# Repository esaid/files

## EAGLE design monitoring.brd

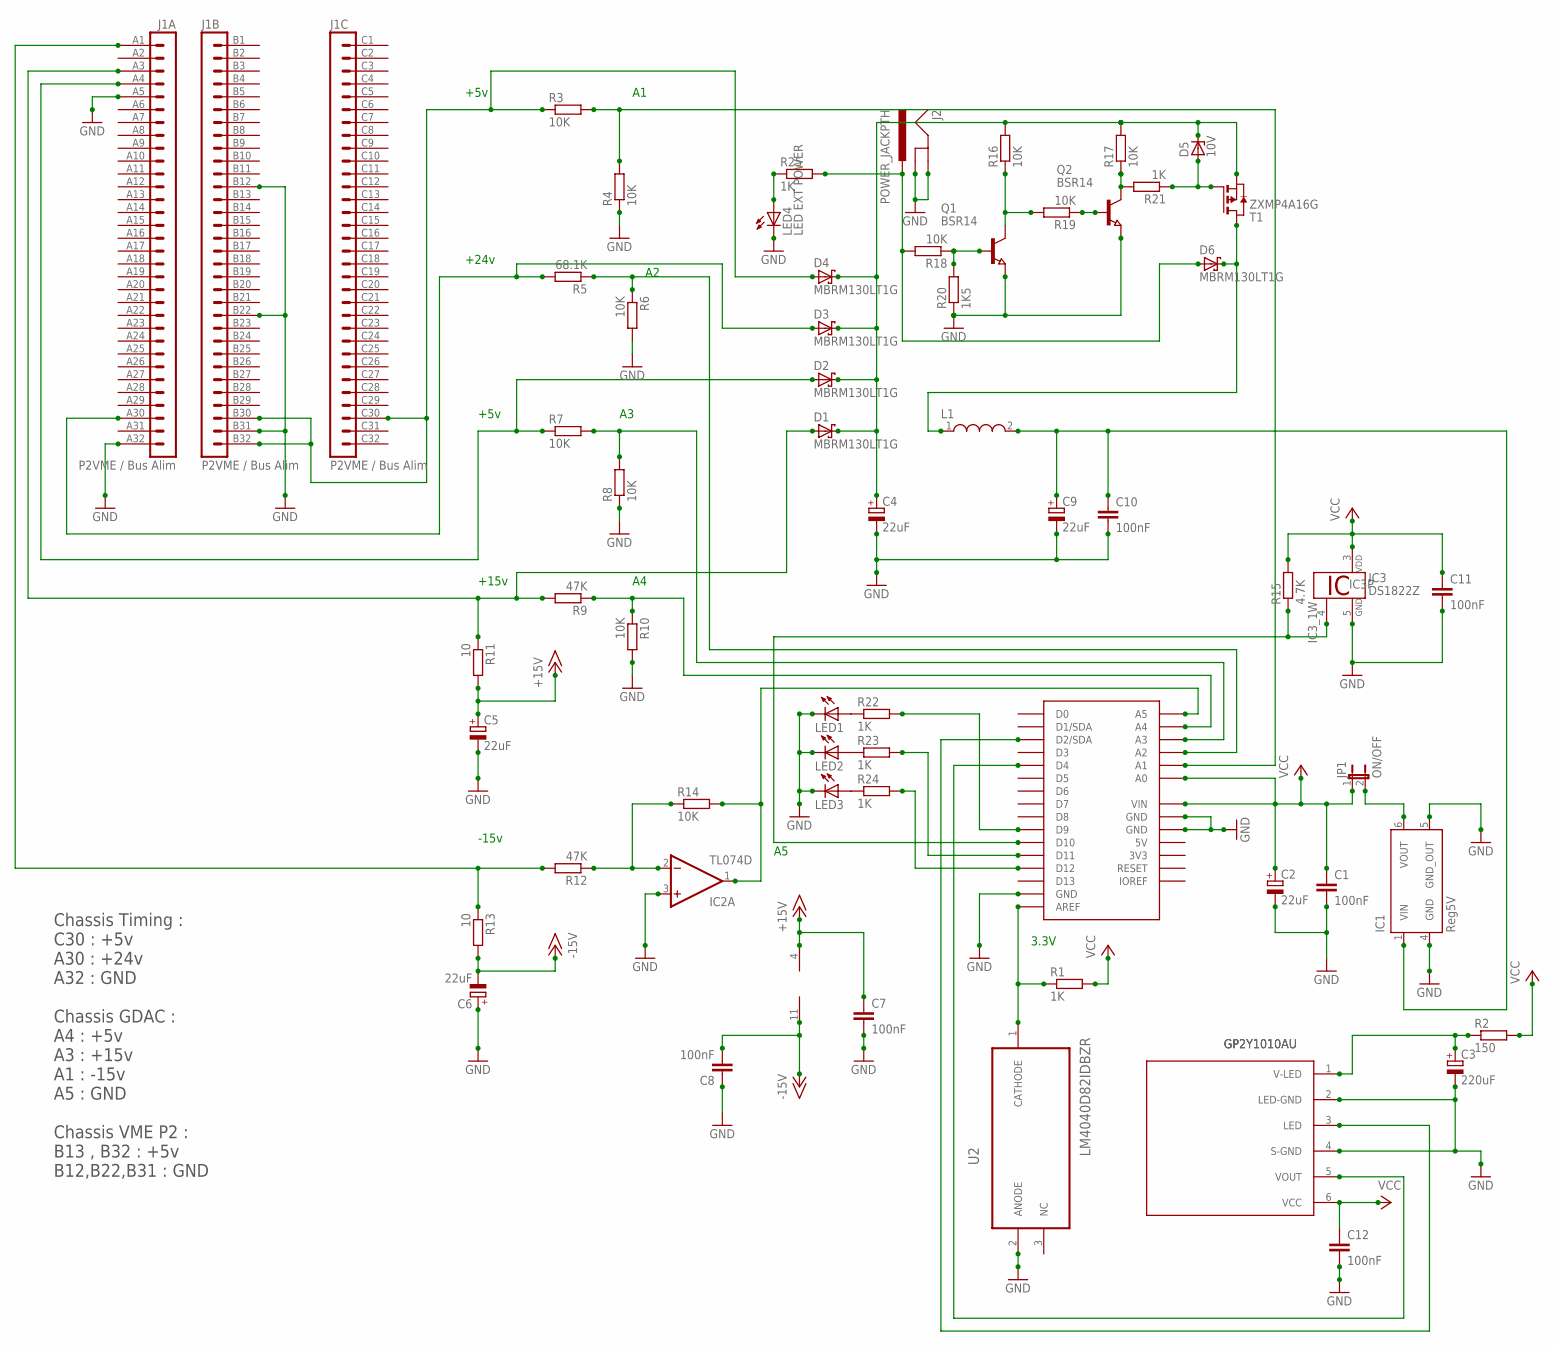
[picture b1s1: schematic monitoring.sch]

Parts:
C1, C7, C8, C10, C11, C12: 100nF; C1206K
C2, C4, C5, C6, C9: 22uF; CT7343
C3: 220uF; 150CLZ-0810
D1, D2, D3, D4, D6: MBRM130LT1G; DIODE_SMB
D5: 10V; SMB
IC1: Reg5V; REG5V
IC2: TL074D; SO14
IC3: DS1822Z; SO08
J1: P2VME / Bus Alim; VG96
J2: POWER_JACKPTH; POWER_JACK_PTH
JP1: ON/OFF; JP1
L1: WE-UKW_1SW_7427501; WE-UKW_7427501
LED1, LED2, LED3: LED_ELD260; LED_LD260
LED4: LED EXT POWER; LED_LD260
Q1, Q2: BSR14; SOT23
R1, R21, R22, R23, R24, R25: 1K; R1206
R2: 150; R1206
R3, R4, R6, R7, R8, R10, R14, R16, R17, R18, R19: 10K; R1206
R5: 68.1K; R1206
R9, R12: 47K; R1206
R11, R13: 10; R1206
R15: 4.7K; R1206
R20: 1K5; R1206
T1: ZXMP4A16G; SOT223
U1: YUN_SHIELD-BPLACE; YUN_SHIELD
U2: LM4040D82IDBZR; SOT95P237X112-3N
U$1: GP2Y1010AU0F; GP2Y1010AU

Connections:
3V3: U1.3V3
5V: U1.5V
+15V: C5.+, C7.1, IC2.4 (V+), R11.2
-15V: C6.-, C8.2, IC2.11 (V-), R13.2
GND: C1.2, C2.-, C3.-, C4.-, C5.-, C6.+, C7.2, C8.1, C9.-, C10.2, C11.2, C12.2, IC1.4 (GND), IC1.5 (GND_OUT), IC2.3 (+IN), IC3.5 (GND), J1.A5 (5), J1.A32 (32), J1.B12 (12), J1.B22 (22), J1.B31 (31), J2.GND, J2.GNDBREAK, LED1.K (C), LED2.K (C), LED3.K (C), LED4.K (C), Q1.2 (E), Q2.2 (E), R4.1, R6.2, R8.1, R10.2, R20.1, U1.GND@1 (GND), U1.GND@2 (GND), U1.GND@3 (GND), U2.2 (ANODE), U$1.2 (LED-GND), U$1.4 (S-GND)
IOREF: U1.IOREF
unnamed: C3.+, R2.1, U$1.1 (V-LED)
unnamed: IC1.6 (VOUT), JP1.2
unnamed: R1.1, U1.AREF, U2.1 (CATHODE)
unnamed: R3.2, R4.2, U1.A1
unnamed: R5.1, R6.1, U1.A2
unnamed: R7.2, R8.2, U1.A3
unnamed: R9.1, R10.1, U1.A4
unnamed: Q1.1 (B), R18.1, R20.2
unnamed: D3.A (C), J1.A30 (30), R5.2
unnamed: D2.A (C), J1.A4 (4), R7.1
unnamed: D1.A (C), J1.A3 (3), R9.2, R11.1
unnamed: C4.+, D1.C (A), D2.C (A), D3.C (A), D4.C (A), D5.C, R16.2, R17.2, T1.3 (S)
unnamed: D4.A (C), J1.B30 (30), J1.B32 (32), J1.C30 (30), R3.1
unnamed: IC2.2 (-IN), R12.1, R14.1
unnamed: J1.A1 (1), R12.2, R13.1
unnamed: IC2.1 (OUT), R14.2, U1.A5
unnamed: D6.C (A), L1.1, T1.2 (D), T1.4 (D)
unnamed: LED1.A, R22.1
unnamed: C9.+, C10.1, IC1.1 (VIN), L1.2
unnamed: Q2.3 (C), R17.1, R21.2
unnamed: Q2.1 (B), R19.1
unnamed: Q1.3 (C), R16.1, R19.2
unnamed: D5.A, R21.1, T1.1 (G)
unnamed: IC3.4 (1W), R15.1, U1.D10
unnamed: U1.D2 (D2/SDA), U$1.3 (LED)
unnamed: U1.D4, U$1.5 (VOUT)
unnamed: D6.A (C), J2.PWR, R18.2, R25.2
unnamed: LED2.A, R23.1
unnamed: LED3.A, R24.1
unnamed: R22.2, U1.D9
unnamed: LED4.A, R25.1
unnamed: R23.2, U1.D11
unnamed: R24.2, U1.D12
VCC: C1.1, C2.+, C11.1, C12.1, IC3.3 (VDD), JP1.1, R1.2, R2.2, R15.2, U1.A0, U1.VIN, U$1.6 (VCC)

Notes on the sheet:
3.3V
+5v
+24v
+15v
-15v
Chassis Timing : C30 : +5v A30 : +24v A32 : GND Chassis GDAC : A4 : +5v A3 : +15v A1 : -15v A5 : GND Chassis VME P2 : B13 , B32 : +5v B12,B22,B31 : GND
GP2Y1010AU

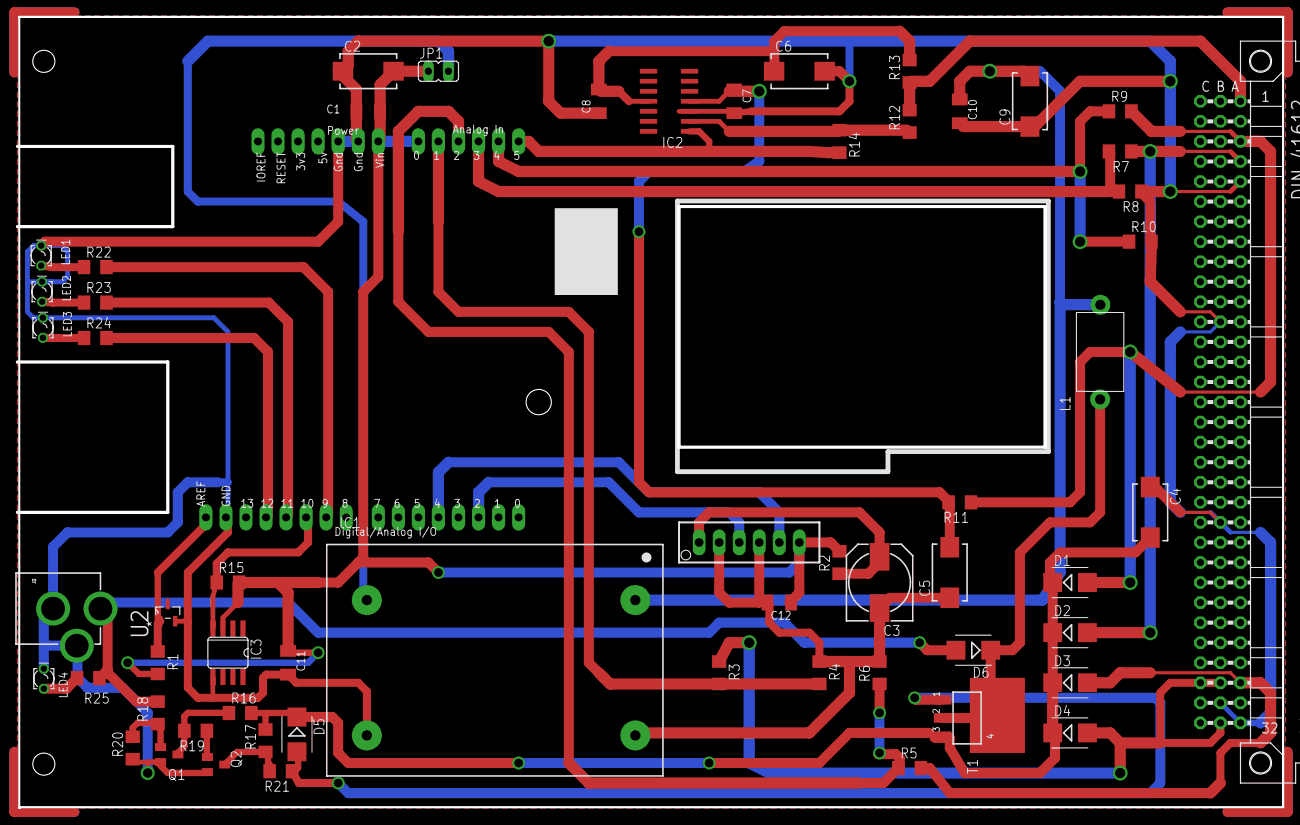
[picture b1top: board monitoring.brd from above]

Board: 8 copper layers, 160.3 x 100.1 mm, 60 parts (0 on the bottom side), 37 nets.

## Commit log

2017-01-23 script bash
    script pour generer des donnees format du fichier csv

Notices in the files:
parts and their libraries:
Eagle_POWER_MAGNETICS_rev16c: Copyright: Würth Elektronik
SparkFun-Connectors: Licensing: Creative Commons ShareAlike 4.0 International - https://creativecommons.org/licenses/by-sa/4.0
